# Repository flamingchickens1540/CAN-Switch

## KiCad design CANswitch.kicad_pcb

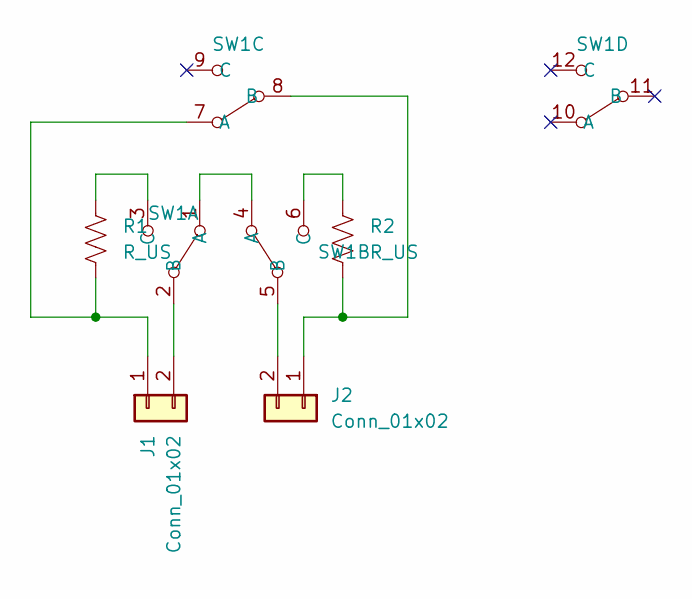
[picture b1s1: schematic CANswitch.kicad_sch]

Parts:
J1, J2: Conn_01x02; WirePad
R1, R2: R_US; R_Axial_DIN0204_L3.6mm_D1.6mm_P7.62mm_Horizontal
SW1: 4PDTThing

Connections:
unnamed: J1.1, R1.2, SW1.7 (A)
unnamed: J1.2, SW1.2 (B)
unnamed: J2.1, R2.2, SW1.8 (B)
unnamed: J2.2, SW1.5 (B)
unnamed: SW1.1 (A), SW1.4 (A)
unnamed: R1.1, SW1.3 (C)
unnamed: R2.1, SW1.6 (C)

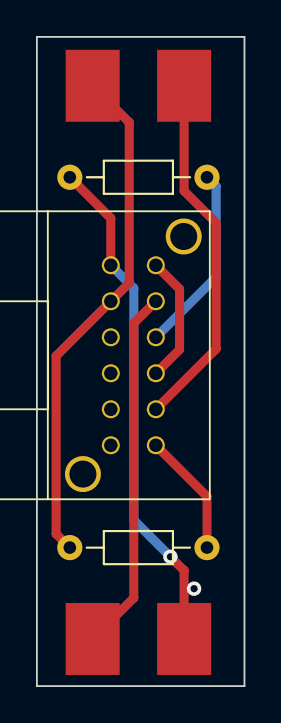
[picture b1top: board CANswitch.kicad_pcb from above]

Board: 2 copper layers, 11.5 x 36.1 mm, 5 parts (0 on the bottom side), 7 nets.

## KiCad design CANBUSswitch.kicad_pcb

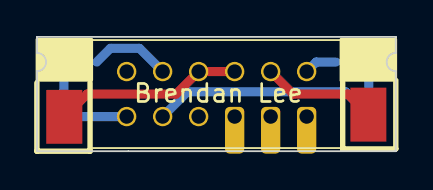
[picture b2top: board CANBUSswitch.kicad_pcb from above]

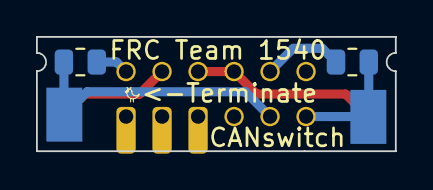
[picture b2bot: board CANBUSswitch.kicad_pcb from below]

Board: 2 copper layers, 19.9 x 6.4 mm, 5 parts (4 on the bottom side), 6 nets.

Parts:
J1, J2: Conn_01x02; WirePad2
R1, R2: R; R_0805_2012Metric
SW1: ★MFS401N−2−Z

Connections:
unnamed: J1.1, R2.1, SW1.8 (B)
unnamed: J1.2, SW1.5 (B)
unnamed: J2.1, R1.2, SW1.7 (A)
unnamed: J2.2, SW1.3 (C), SW1.4 (A)
unnamed: R1.1, SW1.2 (B)
unnamed: R2.2, SW1.6 (C)
